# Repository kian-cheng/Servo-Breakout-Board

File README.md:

# Servo-Breakout-Board
Servo Breakout board separating power and signal supporting up to four channels. Suitable for model rockets and other applications that require the routing of servo cable from another board. <br/>
This repository comprises the Gerber files to manufacture the PCB and KiCad Project files for learning and modifying. 

Schematics: <br/>

PCB Design: <br/>

3D view: <br/>

Designed using KiCad 8.

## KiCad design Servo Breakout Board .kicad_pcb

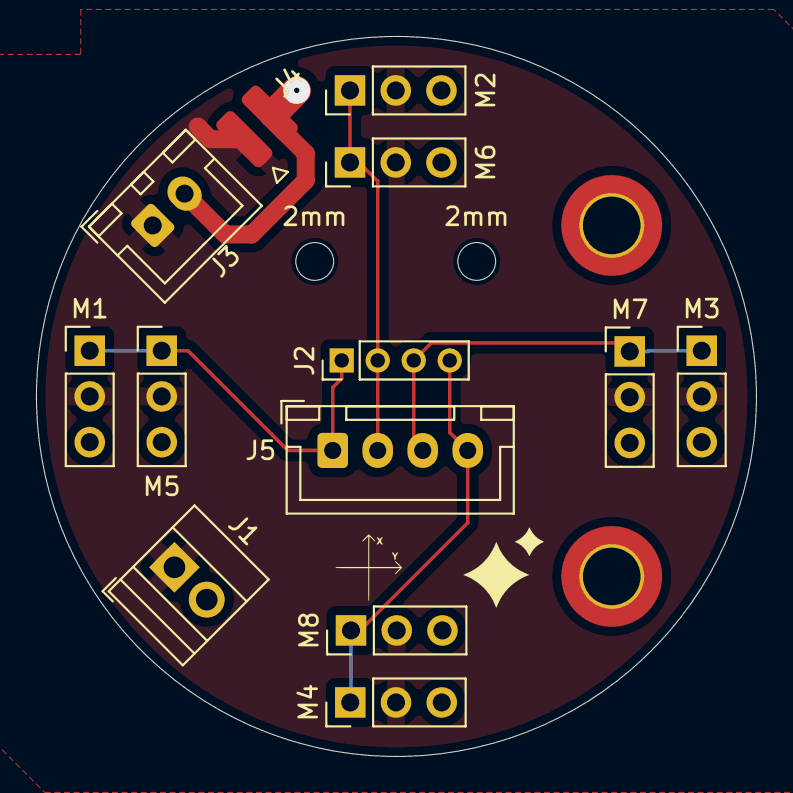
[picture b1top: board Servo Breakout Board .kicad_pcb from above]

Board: 2 copper layers, 40.0 x 40.0 mm, 17 parts (0 on the bottom side), 6 nets.

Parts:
2mm, 2mm#2: MountingHole_2.1mm
J1: Screw_Terminal_01x02; TerminalBlock_Xinya_XY308-2.54-2P_1x02_P2.54mm_Horizontal
J2: Conn_01x04_Pin; PinHeader_1x04_P2.00mm_Vertical
J3: Conn_01x02; JST_XH_B2B-XH-A_1x02_P2.50mm_Vertical
J4: Conn_01x02_Pin; Samtec_UMPS-02-XX.X-X-V-S_1x02_P2.0mm_Socket
J5: Conn_01x04_Pin; JST_XH_B4B-XH-A_1x04_P2.50mm_Vertical
M1, M2, M3#3, M4, M5, M6, M7, M8: Motor_Servo; PinHeader_1x03_P2.54mm_Vertical
M3, M3#2: MountingHole_3.2mm_M3_DIN965_Pad_TopBottom

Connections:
+5V: J1.1, J3.1, J4.1, M1.2 (+), M2.2 (+), M3#3.2 (+), M4.2 (+), M5.2 (+), M6.2 (+), M7.2 (+), M8.2 (+)
GND: J1.2, J3.2, J4.2, M1.3 (-), M2.3 (-), M3#3.3 (-), M4.3 (-), M5.3 (-), M6.3 (-), M7.3 (-), M8.3 (-)
unnamed: J2.1, J5.1, M1.1 (PWM), M5.1 (PWM)
unnamed: J2.2, J5.2, M2.1 (PWM), M6.1 (PWM)
unnamed: J2.3, J5.3, M3#3.1 (PWM), M7.1 (PWM)
unnamed: J2.4, J5.4, M4.1 (PWM), M8.1 (PWM)

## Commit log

2025-01-20 Create KiCad Files
2025-01-20 Create KiCad
2025-01-20 3D model of the PCB
